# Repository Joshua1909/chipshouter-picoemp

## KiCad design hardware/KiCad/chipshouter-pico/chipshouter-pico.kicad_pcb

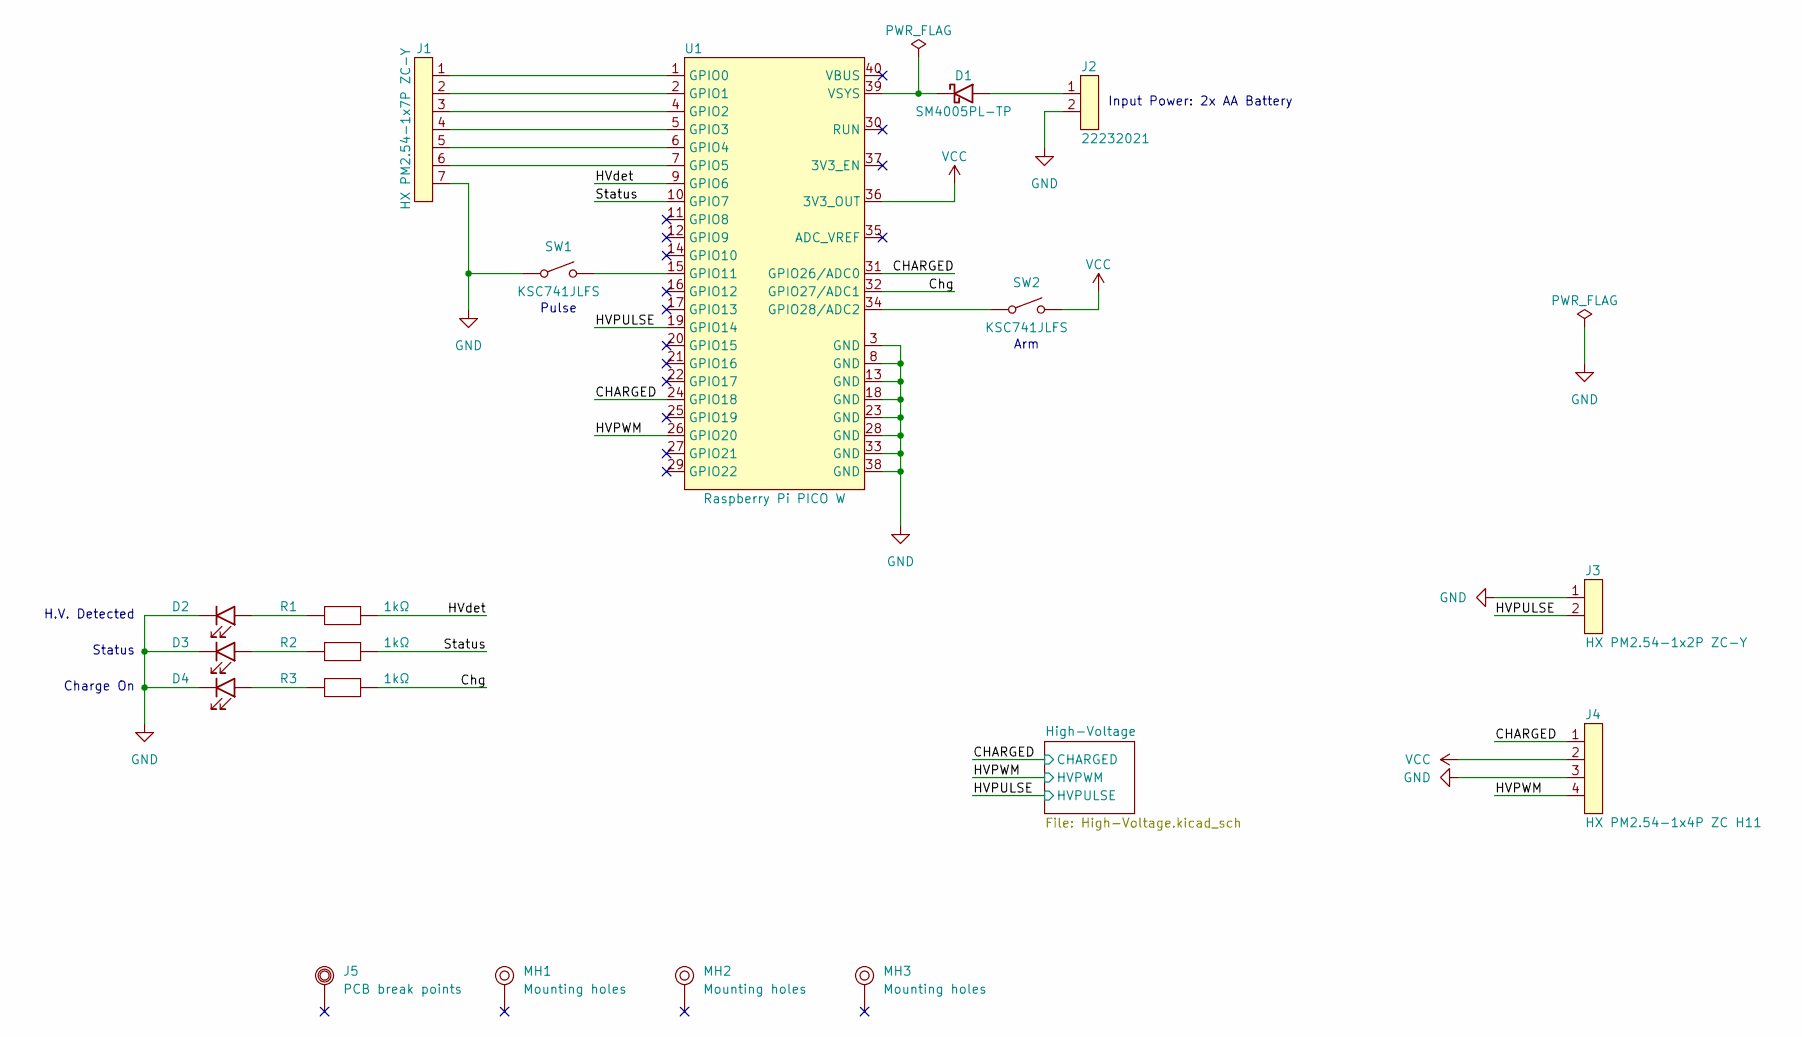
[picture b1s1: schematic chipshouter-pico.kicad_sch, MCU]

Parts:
D1: SM4005PL-TP; Manufacturer Part Numbe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 SM4005PL-TP
D2, D4: LED Red; 19-217/R6C-AL1M2VY/6T; Manufacturer Part Numbe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 19-217/R6C-AL1M2VY/6T
D3: LED Green; 19-219/GHC-YR2T1B5Y/3T; Manufacturer Part Numbe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 19-219/GHC-YR2T1B5Y/3T
J1: HX PM2.54-1x7P ZC-Y; Manufacturer Part Numbe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 HX PM2.54-1x7P ZC-Y
J2: 22232021; Manufacturer Part Numbe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 22232021
J3: HX PM2.54-1x2P ZC-Y; Manufacturer Part Numbe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 HX PM2.54-1x2P ZC-Y
J4: HX PM2.54-1x4P ZC H11; Manufacturer Part Numbe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 HX PM2.54-1x4P ZC H11
J5: PCB break points; PCB BREAK POINTS
MH1, MH2, MH3: Mounting holes; MOUNTING HOLES
R1, R2, R3: 1kΩ; YAGEO_RES0603; Manufacturer Part Numbe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 RC0603FR-071KL
SW1, SW2: KSC741JLFS; Manufacturer Part Numbe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 KSC741JLFS
U1: Raspberry Pi PICO W; Manufacturer Part Numbe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 PICO W

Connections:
/CHARGED: J4.1, U1.24 (GPIO18), U1.31 (GPIO26/ADC0); also elsewhere on the board
/Chg: R3.2, U1.32 (GPIO27/ADC1)
/HVPULSE: J3.2, U1.19 (GPIO14); also elsewhere on the board
/HVPWM: J4.4, U1.26 (GPIO20); also elsewhere on the board
/HVdet: R1.2, U1.9 (GPIO6)
/Status: R2.2, U1.10 (GPIO7)
GND: D2.1 (K), D3.1 (K), D4.1 (K), J1.7, J2.2, J3.1, J4.3, SW1.1, U1.3 (GND), U1.8 (GND), U1.13 (GND), U1.18 (GND), U1.23 (GND), U1.28 (GND), U1.33 (GND), U1.38 (GND); also elsewhere on the board
unnamed: D1.2 (A), J2.1
unnamed: D1.1 (K), U1.39 (VSYS)
unnamed: D2.2 (A), R1.1
unnamed: D3.2 (A), R2.1
unnamed: D4.2 (A), R3.1
unnamed: J1.1, U1.1 (GPIO0)
unnamed: J1.2, U1.2 (GPIO1)
unnamed: J1.3, U1.4 (GPIO2)
unnamed: J1.4, U1.5 (GPIO3)
unnamed: J1.5, U1.6 (GPIO4)
unnamed: J1.6, U1.7 (GPIO5)
unnamed: SW1.2, U1.15 (GPIO11)
unnamed: SW2.1, U1.34 (GPIO28/ADC2)
VCC: J4.2, SW2.2, U1.36 (3V3_OUT); also elsewhere on the board

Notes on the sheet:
Arm
H.V. Detected
Input Power: 2x AA Battery
Status
Charge On
Pulse

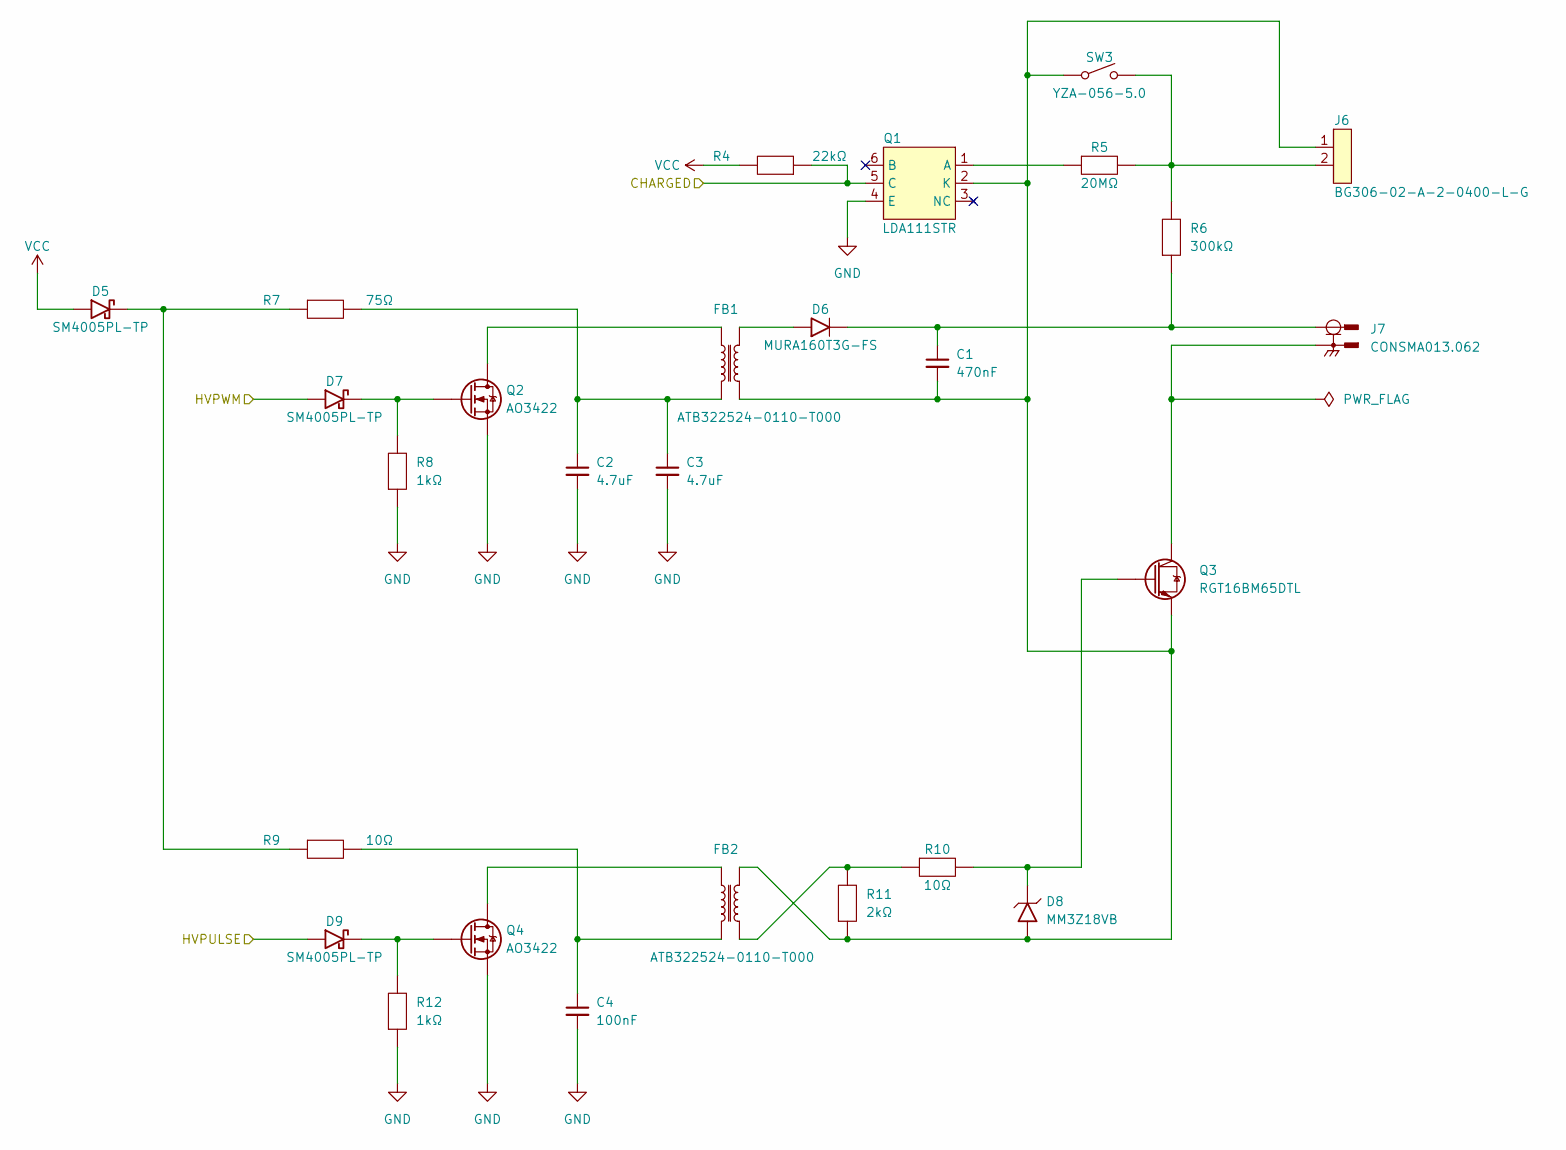
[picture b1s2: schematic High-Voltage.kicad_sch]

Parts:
C1: 470nF; CKG57NX7R2J474MT009W; Manufacturer Part Numbe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 CKG57NX7R2J474MT009W
C2, C3: 4.7uF; CL21A475KBQNNNE; Manufacturer Part Numbe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 CL21A475KBQNNNE
C4: 100nF; C0603C104K5RACTU; Manufacturer Part Numbe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 C0603C104K5RACTU
D5, D7, D9: SM4005PL-TP; Manufacturer Part Numbe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 SM4005PL-TP
D6: MURA160T3G-FS; Manufacturer Part Numbe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 MURA160T3G-FS
D8: MM3Z18VB; Manufacturer Part Numbe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 MM3Z18VB
FB1, FB2: ATB322524-0110-T000; Manufacturer Part Numbe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 ATB322524-0110-T000
J6: BG306-02-A-2-0400-L-G; Manufacturer Part Numbe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 BG306-02-A-2-0400-L-G
J7: CONSMA013.062; Manufacturer Part Numbe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 CONSMA013.062
Q1: LDA111STR; Manufacturer Part Numbe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 LDA111STR
Q2, Q4: AO3422; Manufacturer Part Numbe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 AO3422
Q3: RGT16BM65DTL; Manufacturer Part Numbe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 RGT16BM65DTL
R4: 22kΩ; YAGEO_RES0603; Manufacturer Part Numbe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 RC0603FR-0722KL
R5: 20MΩ; CRMA2010AF20M0FKEF; Manufacturer Part Numbe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 CRMA2010AF20M0FKEF
R6: 300kΩ; 3522300KFT; Manufacturer Part Numbe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 3522300KFT
R7: 75Ω; YAGEO_RES0603; Manufacturer Part Numbe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 RC0603JR-0775RL
R8, R12: 1kΩ; YAGEO_RES0603; Manufacturer Part Numbe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 RC0603FR-071KL
R9, R10: 10Ω; YAGEO_RES0603; Manufacturer Part Numbe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 RC0603FR-0710RL
R11: 2kΩ; YAGEO_RES0603; Manufacturer Part Numbe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 RC0603FR-072KL
SW3: YZA-056-5.0; Manufacturer Part Numbe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 YZA-056-5.0

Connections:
/CHARGED: Q1.5 (C), R4.1; also elsewhere on the board
/HVPULSE: D9.2 (A); also elsewhere on the board
/HVPWM: D7.2 (A); also elsewhere on the board
GND: C2.2, C3.2, C4.2, Q1.4 (E), Q2.2 (S), Q4.2 (S), R8.1, R12.1; also elsewhere on the board
unnamed: C2.1, C3.1, FB1.4, R7.2
unnamed: C4.1, FB2.4, R9.2
unnamed: D5.1 (K), R7.1, R9.1
unnamed: D6.2 (A), FB1.2
unnamed: C1.1, D6.1 (K), J7.1 (SIG), R6.1
unnamed: D7.1 (K), Q2.1 (G), R8.2
unnamed: C1.2, D8.1 (A), FB1.3, FB2.2, J6.1, Q1.2 (K), Q3.3 (E), R11.1, SW3.1
unnamed: D8.2 (K), Q3.1 (G), R10.2
unnamed: D9.1 (K), Q4.1 (G), R12.2
unnamed: FB2.3, R10.1, R11.2
unnamed: J6.2, R5.2, R6.2, SW3.2
unnamed: J7.2 (SH), Q3.4 (C)
unnamed: Q1.1 (A), R5.1
unnamed: FB1.1, Q2.3 (D)
unnamed: FB2.1, Q4.3 (D)
VCC: D5.2 (A), R4.2; also elsewhere on the board

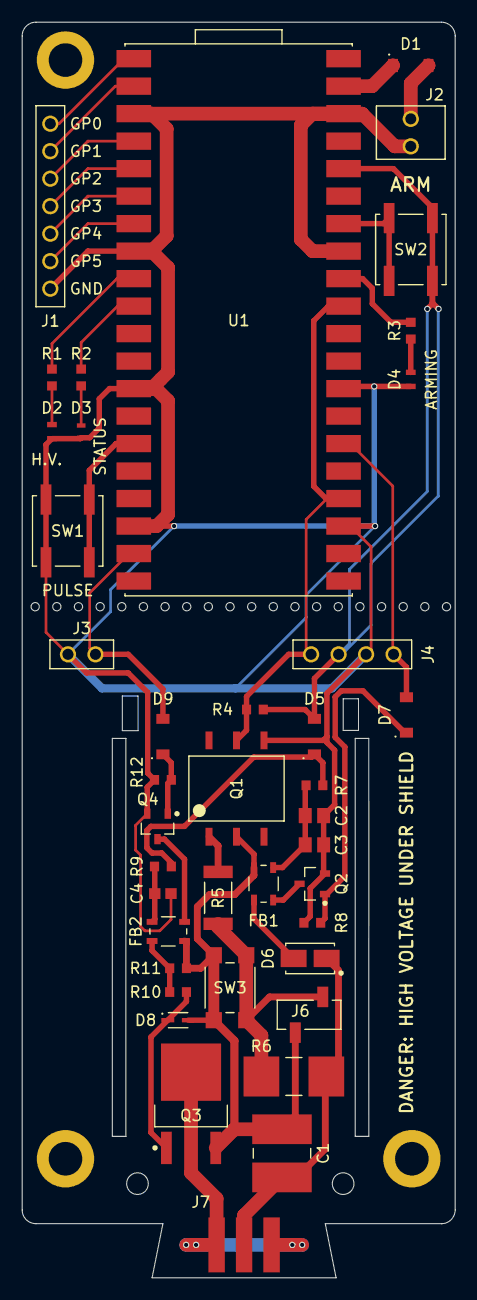
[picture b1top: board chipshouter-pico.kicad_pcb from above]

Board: 2 copper layers, 40.0 x 116.0 mm, 45 parts (0 on the bottom side), 36 nets.
